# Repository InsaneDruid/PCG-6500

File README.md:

# PCG 6500 - a HAL clone
The PCG 6500 is a 100% compatible clone of the programmable character set generator and sound device for the CBM PET series computers.
It implements all the features, including the ability to reprogram 64 of the PET characters into custom graphics, as well as support for amplified CB2 sound output.

[Schematic](https://github.com/InsaneDruid/PCG-6500/blob/main/6500_board/pcg6500.pdf "Schematic")  

[Bill of Materials](https://htmlpreview.github.io/?https://github.com/InsaneDruid/PCG-6500/blob/main/6500_board/bom/pcg6500_bom.html "Bill of Materials")

## The 6540 Adapter

For PETs using the MOS 6540 rom set, there is an [adapter board](https://github.com/InsaneDruid/PCG-6500/blob/main/6540_adapter "adapter board") that mounts in place of CN1 and allows easy connection to the 6540 charrom using two DIP 28pin to ribbon adapters.

## The SwitchMod
Originally, there was no way to simply disable the HAL PCG 6500 once installed. Katunori Takesita discovered a simple modification that an owner had applied to his board, which consisted of disconnecting an input of a nand-gate from address 9 of the CharROM bus (by cutting a trace) and grounding it instead, effectively disabling the RAM and re-enabling the CharROM permanently. This mod is also implemented in this replica and jumper JP1 is provided for this purpose.

### Enabling the card permanently
Bridge JP1 to permanently enable the card like it was originally.

### The SwitchMod board
A small [SwitchMod board](https://github.com/InsaneDruid/PCG-6500/blob/main/6500_switchMod "SwitchMod board") has been designed providing the ability to switch between the address9 signal and GND for the input of IC8D using an 74LS00, avoiding the need to route the fast address signal over a mechanical switch. This board also has the ability to connect a 3-pin common cathode dual LED (or one or two standard LEDs) to indicate the state of the board. Connect the pins E,A,+,- on the SwitchMod to the corresponding pins on the 6500 board.

## The case
A [3d printable case](https://www.printables.com/model/819722-hal-pcg-6500-case "https://www.printables.com/model/819722-hal-pcg-6500-case") is available at my printables profile.

## Programming the PCG 6500 
Each programmable character provided by the PCG 6500 is programmed line by line via the PETs 6522 peripheral port A (PA7-0), which is available on the user port. PA0-4 transport the actual data, PA 5-7 address the data and address latches on the PCG 6500
See the [Programming chart](https://github.com/InsaneDruid/PCG-6500/blob/main/6500_programming_chart.pdf "Programming chart") originally taken from the PCG 6500 manual with some fixed typos.

## The Software
Software using the PCG-6500 and further documents are available on their own repository: [PCG-6500 Software](https://github.com/InsaneDruid/PCG-6500-Software "Software and Documents for the PCG-6500 Software")

## The License
This work is licensed under a Creative Commons Attribution-ShareAlike 4.0 International License.  
See https://creativecommons.org/licenses/by-sa/4.0/.

## The Credits
This work would not have been possible without the help from a bunch of amazing people from [VzEkC e. V. forums](https://forum.classic-computing.de/forum/ "forum.classic-computing.de") and around the world. Many thanks go out to:

* *AndyG* - for providing images of a working board.
* *Katunori Takesita* - his blog about repairing an original board had important additional images and informations.

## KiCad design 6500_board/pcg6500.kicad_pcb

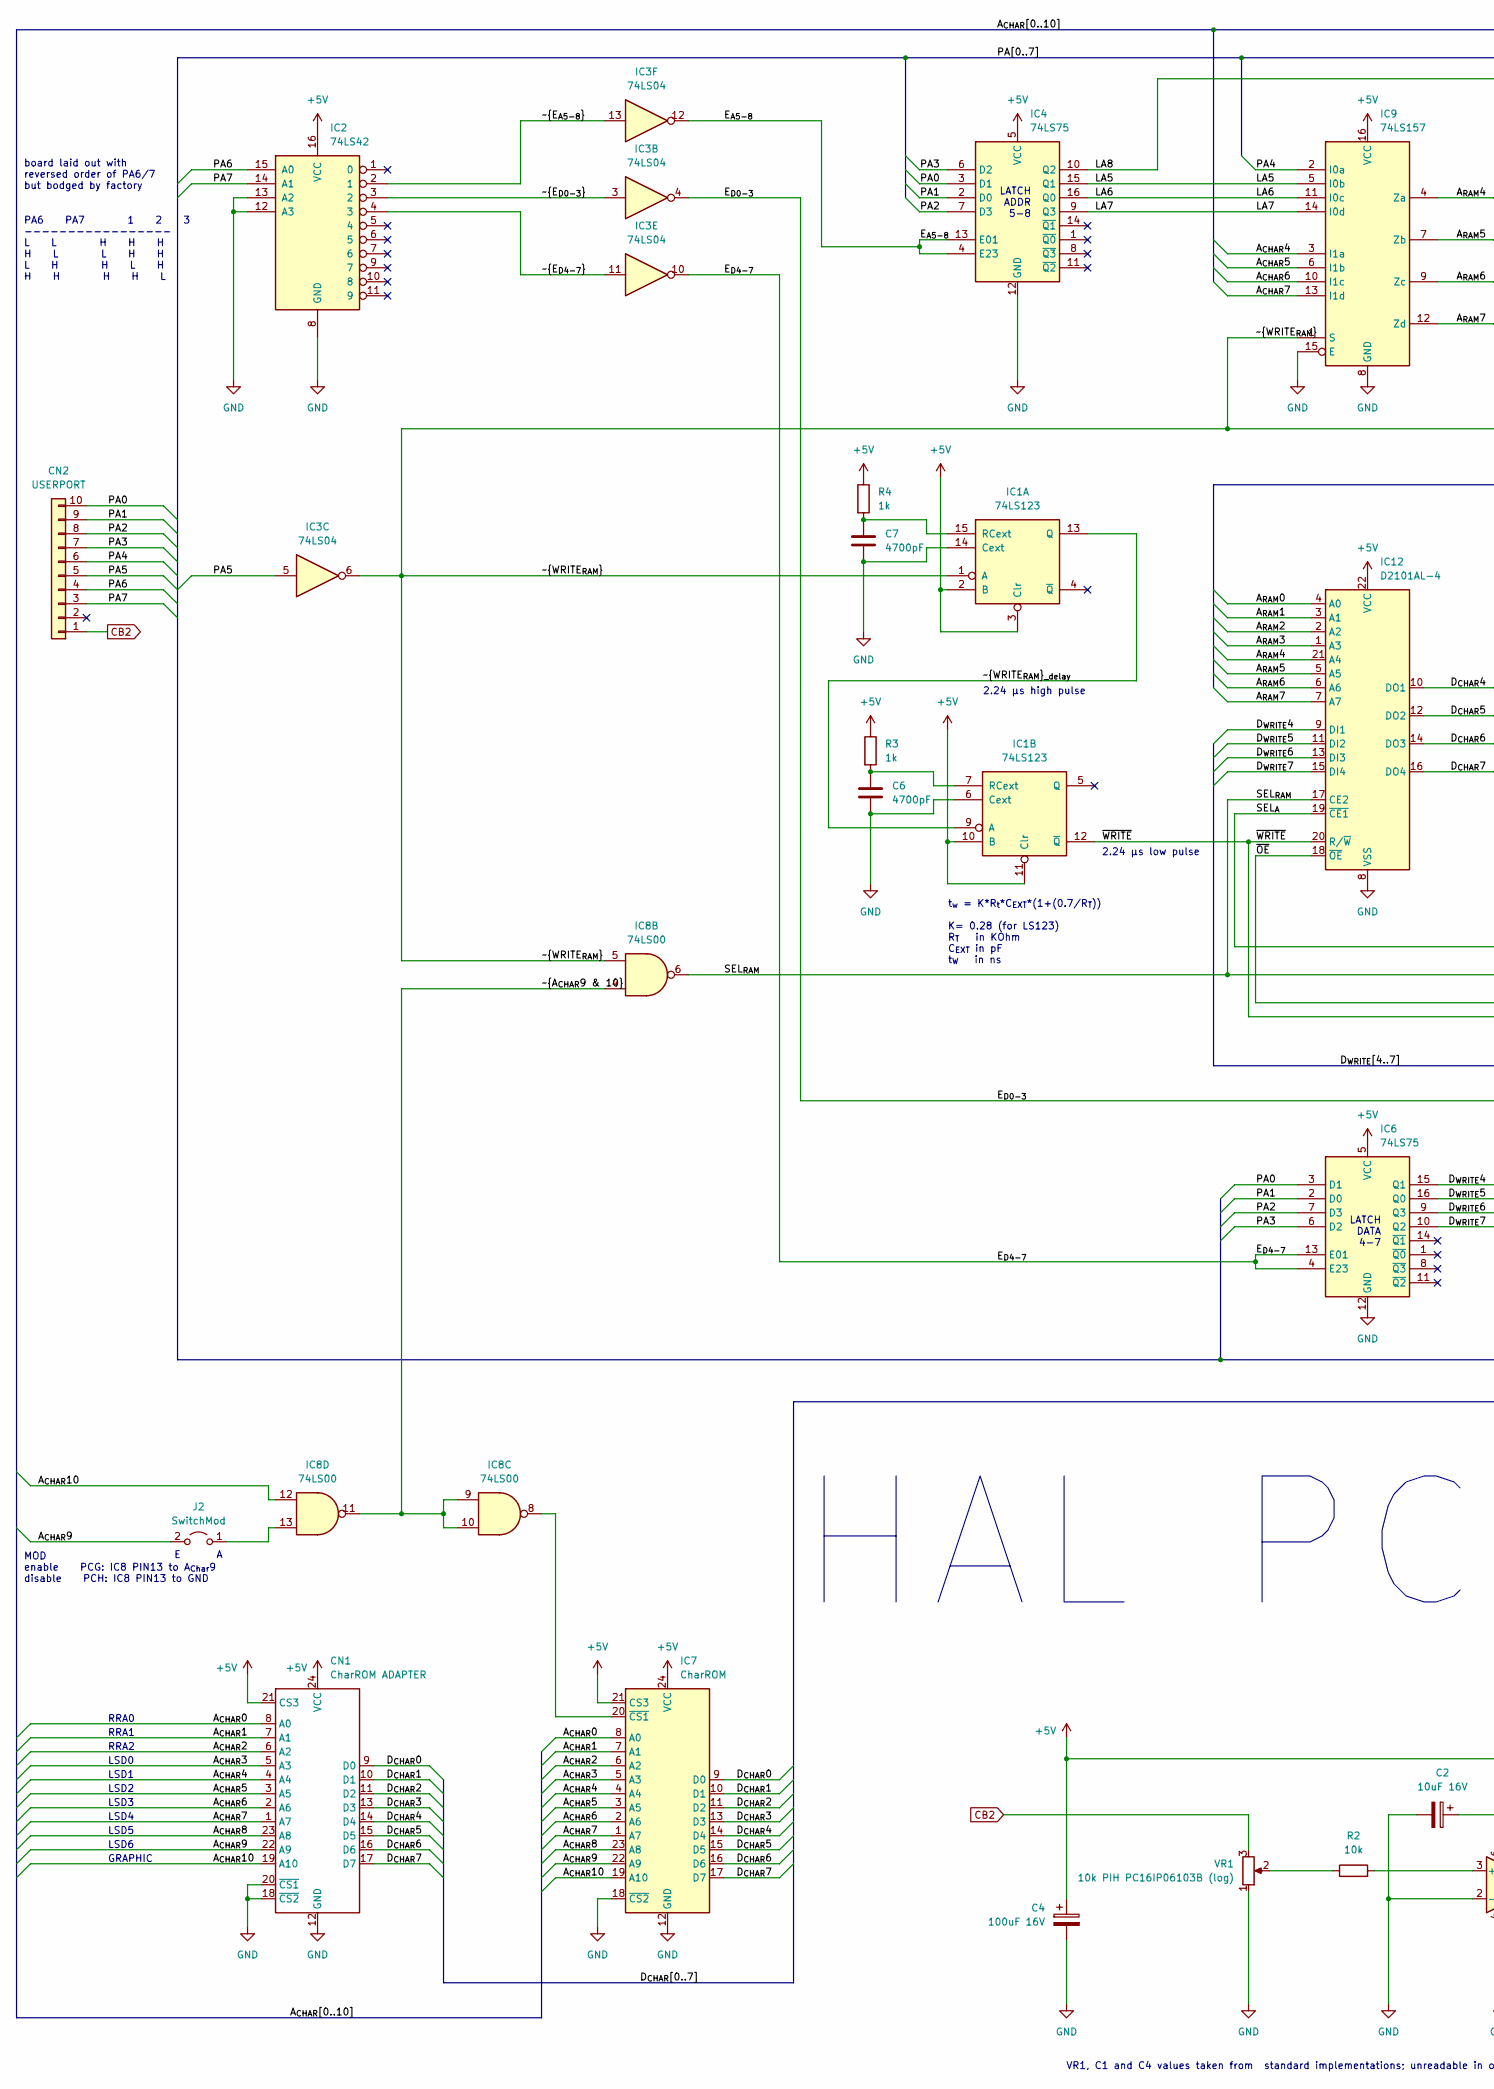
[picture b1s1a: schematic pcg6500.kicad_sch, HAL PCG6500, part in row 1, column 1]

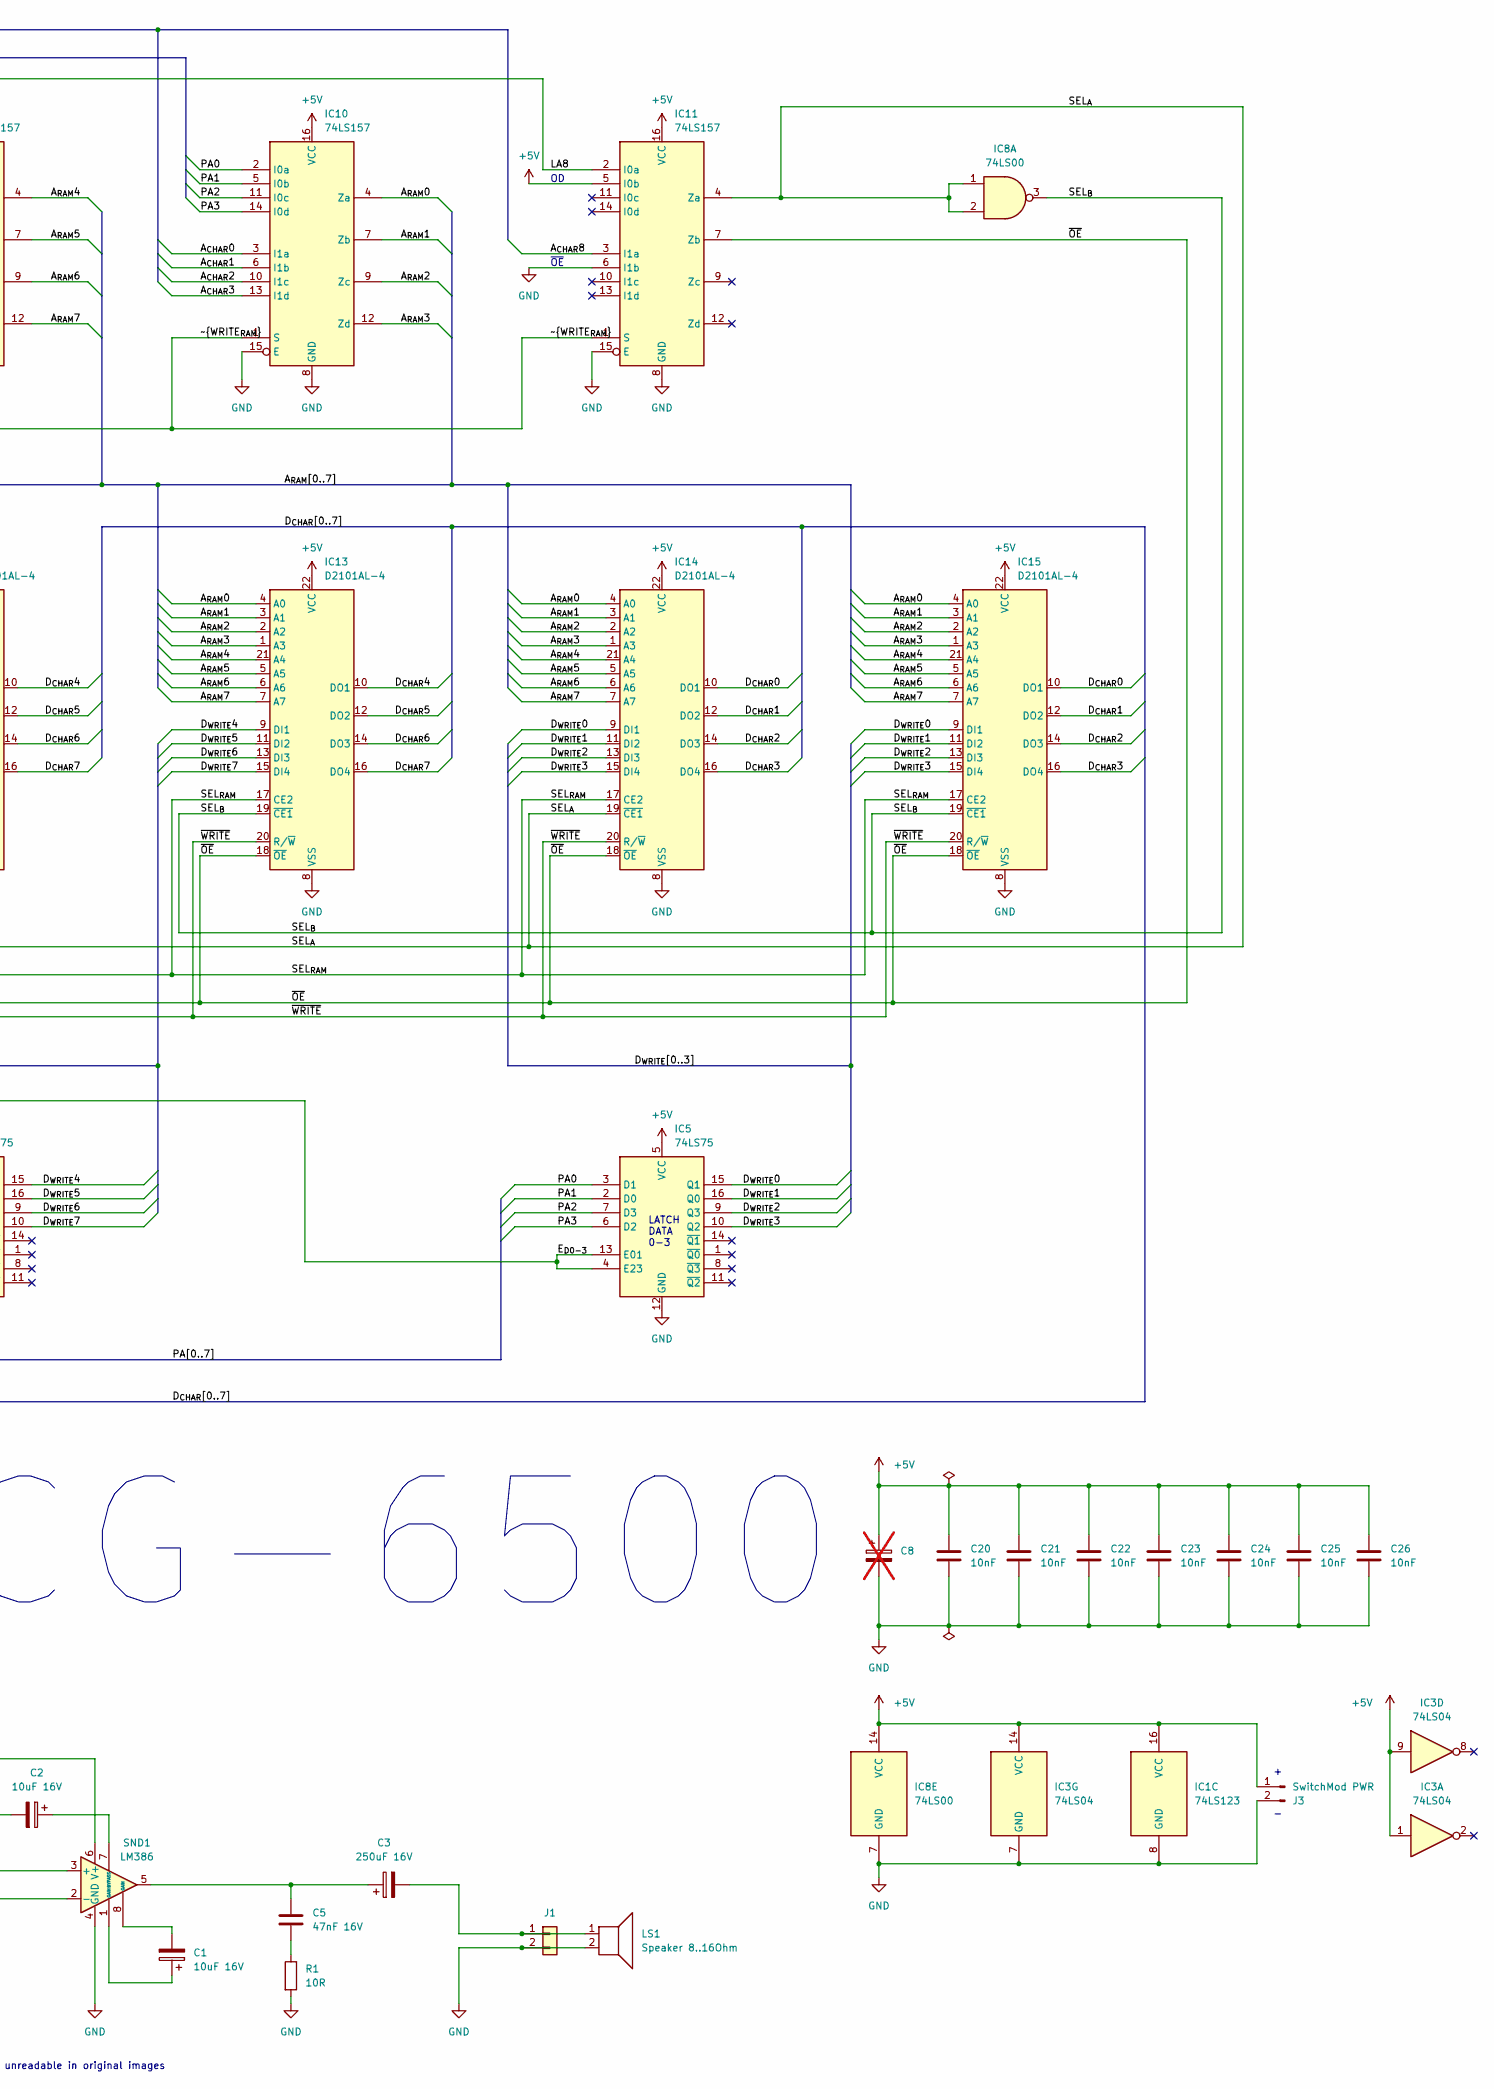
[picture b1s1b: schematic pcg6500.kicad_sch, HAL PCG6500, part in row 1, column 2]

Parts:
C1, C2: 10uF 16V; CP_Radial_D6.3mm_P2.50mm
C3: 250uF 16V; CP_Radial_D10.0mm_P5.00mm
C4: 100uF 16V; CP_Radial_D8.0mm_P5.00mm
C5: 47nF 16V; C_Disc_D4.3mm_W1.9mm_P7.62mm
C6, C7: 4700pF; C_Disc_D4.3mm_W1.9mm_P5.08mm
C8: C_Polarized; CP_Radial_D8.0mm_P5.00mm; not fitted
C20, C21, C22, C23, C24, C25, C26: 10nF; C_Disc_D4.3mm_W1.9mm_P5.08mm_dualpad
CN1: CharROM ADAPTER; DIP-24_W15.24mm_Wire_Adapter
CN2: USERPORT; PinHeader_1x10_P2.54mm_Vertical
IC1: 74LS123; DIP-16_W7.62mm
IC2: 74LS42; DIP-16_W7.62mm
IC3: 74LS04; DIP-14_W7.62mm
IC4, IC5, IC6: 74LS75; DIP-16_W7.62mm
IC7: CharROM; DIP-24_W15.24mm_Socket
IC8: 74LS00; DIP-14_W7.62mm
IC9, IC10, IC11: 74LS157; DIP-16_W7.62mm
IC12, IC13, IC14, IC15: D2101AL-4; DIP-22_W10.16mm
J1: Speaker 8..16Ohm; SolderWire-1sqmm_1x02_P7.8mm_D1.4mm_OD3.9mm
J2: SwitchMod; PinHeader_1x02_P2.54mm_Horizontal
J3: SwitchMod PWR; PinHeader_1x02_P2.54mm_Horizontal
LS1: Speaker 8..16Ohm
R1: 10R; R_Axial_DIN0207_L6.3mm_D2.5mm_P9.2075mm_Horizontal
R2: 10k; R_Axial_DIN0309_L9.0mm_D3.2mm_P12.70mm_Horizontal
R3, R4: 1k; R_Axial_DIN0207_L6.3mm_D2.5mm_P9.2075mm_Horizontal
SND1: LM386; DIP-8_W7.62mm
VR1: 10k PIH PC16IP06103B (log); Potentiometer_Piher_PC-16_Dual_Horizontal

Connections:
+5V: C4.1, C8.1, C20.1, C21.1, C22.1, C23.1, C24.1, C25.2, C26.2, CN1.21 (CS3), CN1.24 (VCC), IC1.2 (B), IC1.3 (Clr), IC1.10 (B), IC1.11 (Clr), IC1.16 (VCC), IC2.16 (VCC), IC3.1, IC3.9, IC3.14 (VCC), IC4.5 (VCC), IC5.5 (VCC), IC6.5 (VCC), IC7.21 (CS3), IC7.24 (VCC), IC8.14 (VCC), IC9.16 (VCC), IC10.16 (VCC), IC11.5 (I0b), IC11.16 (VCC), IC12.22 (VCC), IC13.22 (VCC), IC14.22 (VCC), IC15.22 (VCC), J3.1, R3.1, R4.1, SND1.6 (V+)
/A_{CHAR}0: CN1.8 (A0), IC7.8 (A0), IC10.3 (I1a)
/A_{CHAR}1: CN1.7 (A1), IC7.7 (A1), IC10.6 (I1b)
/A_{CHAR}2: CN1.6 (A2), IC7.6 (A2), IC10.10 (I1c)
/A_{CHAR}3: CN1.5 (A3), IC7.5 (A3), IC10.13 (I1d)
/A_{CHAR}4: CN1.4 (A4), IC7.4 (A4), IC9.3 (I1a)
/A_{CHAR}5: CN1.3 (A5), IC7.3 (A5), IC9.6 (I1b)
/A_{CHAR}6: CN1.2 (A6), IC7.2 (A6), IC9.10 (I1c)
/A_{CHAR}7: CN1.1 (A7), IC7.1 (A7), IC9.13 (I1d)
/A_{CHAR}8: CN1.23 (A8), IC7.23 (A8), IC11.3 (I1a)
/A_{CHAR}9: CN1.22 (A9), IC7.22 (A9), J2.2 (B)
/A_{CHAR}10: CN1.19 (A10), IC7.19 (A10), IC8.12
/A_{RAM}0: IC10.4 (Za), IC12.4 (A0), IC13.4 (A0), IC14.4 (A0), IC15.4 (A0)
/A_{RAM}1: IC10.7 (Zb), IC12.3 (A1), IC13.3 (A1), IC14.3 (A1), IC15.3 (A1)
/A_{RAM}2: IC10.9 (Zc), IC12.2 (A2), IC13.2 (A2), IC14.2 (A2), IC15.2 (A2)
/A_{RAM}3: IC10.12 (Zd), IC12.1 (A3), IC13.1 (A3), IC14.1 (A3), IC15.1 (A3)
/A_{RAM}4: IC9.4 (Za), IC12.21 (A4), IC13.21 (A4), IC14.21 (A4), IC15.21 (A4)
/A_{RAM}5: IC9.7 (Zb), IC12.5 (A5), IC13.5 (A5), IC14.5 (A5), IC15.5 (A5)
/A_{RAM}6: IC9.9 (Zc), IC12.6 (A6), IC13.6 (A6), IC14.6 (A6), IC15.6 (A6)
/A_{RAM}7: IC9.12 (Zd), IC12.7 (A7), IC13.7 (A7), IC14.7 (A7), IC15.7 (A7)
/D_{CHAR}0: CN1.9 (D0), IC7.9 (D0), IC14.10 (DO1), IC15.10 (DO1)
/D_{CHAR}1: CN1.10 (D1), IC7.10 (D1), IC14.12 (DO2), IC15.12 (DO2)
/D_{CHAR}2: CN1.11 (D2), IC7.11 (D2), IC14.14 (DO3), IC15.14 (DO3)
/D_{CHAR}3: CN1.13 (D3), IC7.13 (D3), IC14.16 (DO4), IC15.16 (DO4)
/D_{CHAR}4: CN1.14 (D4), IC7.14 (D4), IC12.10 (DO1), IC13.10 (DO1)
/D_{CHAR}5: CN1.15 (D5), IC7.15 (D5), IC12.12 (DO2), IC13.12 (DO2)
/D_{CHAR}6: CN1.16 (D6), IC7.16 (D6), IC12.14 (DO3), IC13.14 (DO3)
/D_{CHAR}7: CN1.17 (D7), IC7.17 (D7), IC12.16 (DO4), IC13.16 (DO4)
/D_{WRITE}0: IC5.15 (Q1), IC14.9 (DI1), IC15.9 (DI1)
/D_{WRITE}1: IC5.16 (Q0), IC14.11 (DI2), IC15.11 (DI2)
/D_{WRITE}2: IC5.9 (Q3), IC14.13 (DI3), IC15.13 (DI3)
/D_{WRITE}3: IC5.10 (Q2), IC14.15 (DI4), IC15.15 (DI4)
/D_{WRITE}4: IC6.15 (Q1), IC12.9 (DI1), IC13.9 (DI1)
/D_{WRITE}5: IC6.16 (Q0), IC12.11 (DI2), IC13.11 (DI2)
/D_{WRITE}6: IC6.9 (Q3), IC12.13 (DI3), IC13.13 (DI3)
/D_{WRITE}7: IC6.10 (Q2), IC12.15 (DI4), IC13.15 (DI4)
/E_{A5-8}: IC3.12, IC4.4 (E23), IC4.13 (E01)
/E_{D0-3}: IC3.4, IC5.4 (E23), IC5.13 (E01)
/E_{D4-7}: IC3.10, IC6.4 (E23), IC6.13 (E01)
/LA5: IC4.15 (Q1), IC9.5 (I0b)
/LA6: IC4.16 (Q0), IC9.11 (I0c)
/LA7: IC4.9 (Q3), IC9.14 (I0d)
/LA8: IC4.10 (Q2), IC11.2 (I0a)
/PA0: CN2.10, IC4.3 (D1), IC5.3 (D1), IC6.3 (D1), IC10.2 (I0a)
/PA1: CN2.9, IC4.2 (D0), IC5.2 (D0), IC6.2 (D0), IC10.5 (I0b)
/PA2: CN2.8, IC4.7 (D3), IC5.7 (D3), IC6.7 (D3), IC10.11 (I0c)
/PA3: CN2.7, IC4.6 (D2), IC5.6 (D2), IC6.6 (D2), IC10.14 (I0d)
/PA4: CN2.6, IC9.2 (I0a)
/PA5: CN2.5, IC3.5
/PA6: CN2.4, IC2.15 (A0)
/PA7: CN2.3, IC2.14 (A1)
/SEL_{A}: IC8.1, IC8.2, IC11.4 (Za), IC12.19 (~CE1), IC14.19 (~CE1)
/SEL_{B}: IC8.3, IC13.19 (~CE1), IC15.19 (~CE1)
/SEL_{RAM}: IC8.6, IC12.17 (CE2), IC13.17 (CE2), IC14.17 (CE2), IC15.17 (CE2)
/~A_{CHAR9 & 10}: IC8.4, IC8.9, IC8.10, IC8.11
/~E_{A5-8}: IC2.2 (1), IC3.13
/~E_{D0-3}: IC2.3 (2), IC3.3
/~E_{D4-7}: IC2.4 (3), IC3.11
/~OE: IC11.7 (Zb), IC12.18 (~OE), IC13.18 (~OE), IC14.18 (~OE), IC15.18 (~OE)
/~WRITE_{RAM}: IC1.1 (A), IC3.6, IC8.5, IC9.1 (S), IC10.1 (S), IC11.1 (S)
/~WRITE_{RAM}_{_delay}: IC1.9 (A), IC1.13 (Q)
/~WRITE: IC1.12 (~Q), IC12.20 (R/~W), IC13.20 (R/~W), IC14.20 (R/~W), IC15.20 (R/~W)
CB2: CN2.1, VR1.3
GND: C2.2, C4.2, C6.2, C7.2, C8.2, C20.2, C21.2, C22.2, C23.2, C24.2, C25.1, C26.1, CN1.12 (GND), CN1.18 (~CS2), CN1.20 (~CS1), IC1.6 (Cext), IC1.8 (GND), IC1.14 (Cext), IC2.8 (GND), IC2.12 (A3), IC2.13 (A2), IC3.7 (GND), IC4.12 (GND), IC5.12 (GND), IC6.12 (GND), IC7.12 (GND), IC7.18 (~CS2), IC8.7 (GND), IC9.8 (GND), IC9.15 (E), IC10.8 (GND), IC10.15 (E), IC11.6 (I1b), IC11.8 (GND), IC11.15 (E), IC12.8 (VSS), IC13.8 (VSS), IC14.8 (VSS), IC15.8 (VSS), J1.2, J1.12, J1.18, J1.20, J3.2, LS1.2, R1.2, SND1.2 (-), SND1.4 (GND), VR1.1
unnamed: C1.1, SND1.1 (GAIN)
unnamed: C1.2, SND1.8 (GAIN)
unnamed: C3.1, C5.1, SND1.5
unnamed: C5.2, R1.1
unnamed: C7.1, IC1.15 (RCext), R4.2
unnamed: C6.1, IC1.7 (RCext), R3.2
unnamed: IC7.20 (~CS1), IC8.8
unnamed: C3.2, J1.1, LS1.1
unnamed: IC8.13, J2.1 (A)
unnamed: R2.1, VR1.2
unnamed: R2.2, SND1.3 (+)
unnamed: C2.1, SND1.7 (BYPASS)

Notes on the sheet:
LATCH DATA 4-7
board laid out with reversed order of PA6/7 but bodged by factory
LATCH DATA 0-3
LSD2
LATCH ADDR 5-8
2.24 µs low pulse
t_{w} = K*R_{t}*C_{EXT}*(1+(0.7/R_{T})) K= 0.28 (for LS123) R_{T} in KOhm C_{EXT} in pF t_{W} in ns
RRA2
RRA1
GRAPHIC
LSD1
RRA0
LSD0
2.24 µs high pulse
HAL PCG-6500
LSD6
LSD3
LSD5
~{OE}
MOD enable PCG: IC8 PIN13 to A_{Char}9 disable PCH: IC8 PIN13 to GND
LSD4
VR1, C1 and C4 values taken from standard implementations; unreadable in original images
PA6 PA7 1 2 3 ----------------- L L H H H H L L H H L H H L H H H H H L

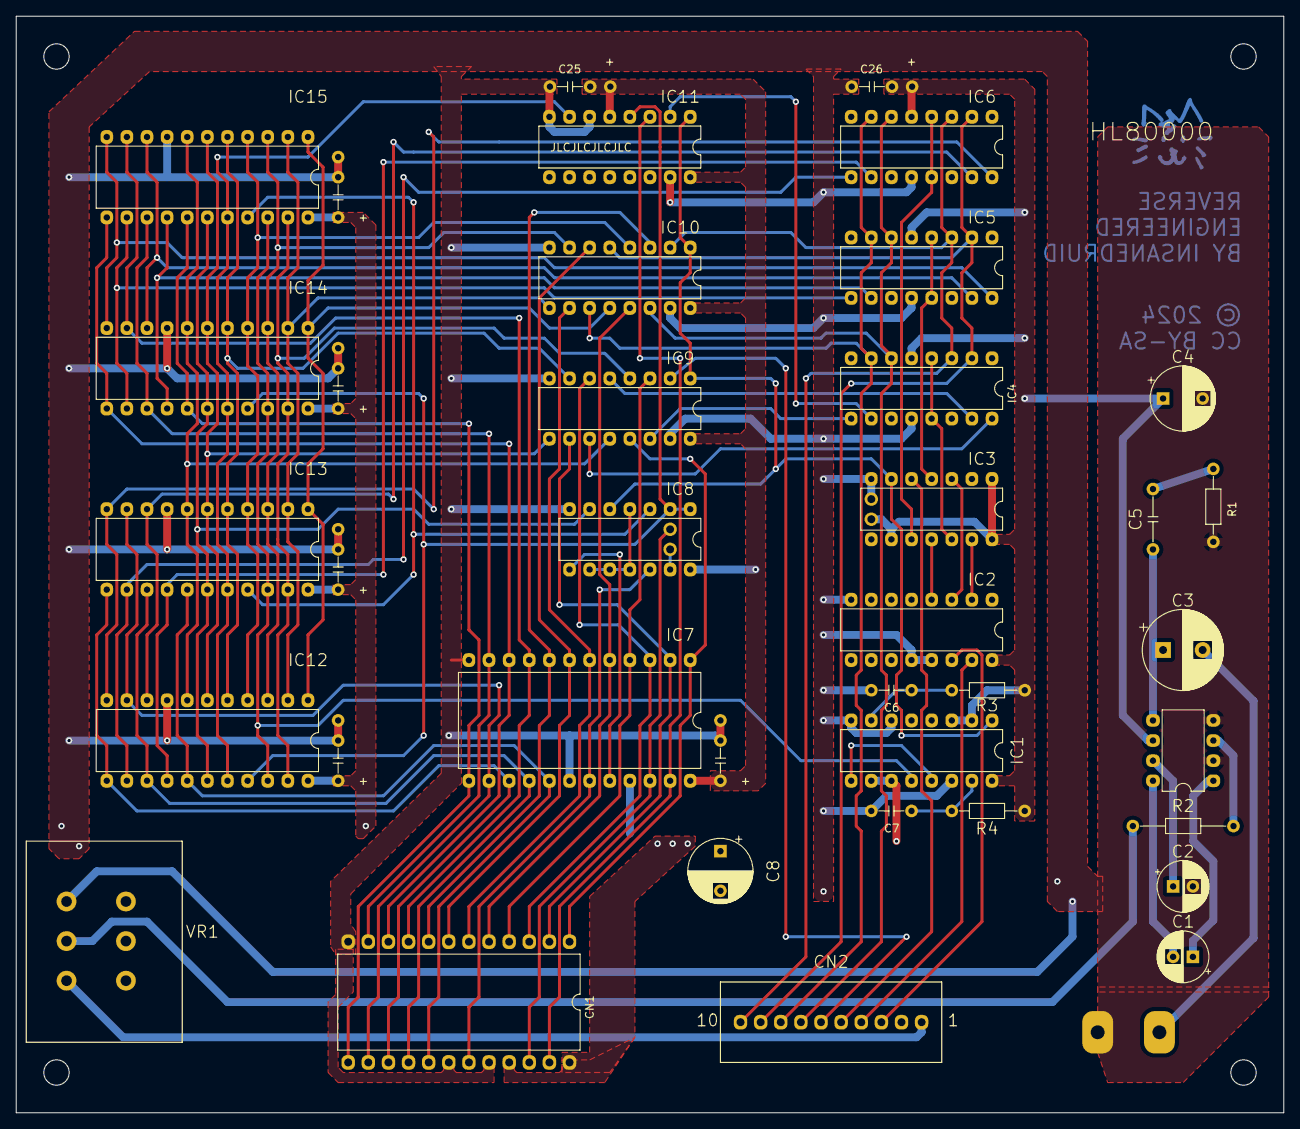
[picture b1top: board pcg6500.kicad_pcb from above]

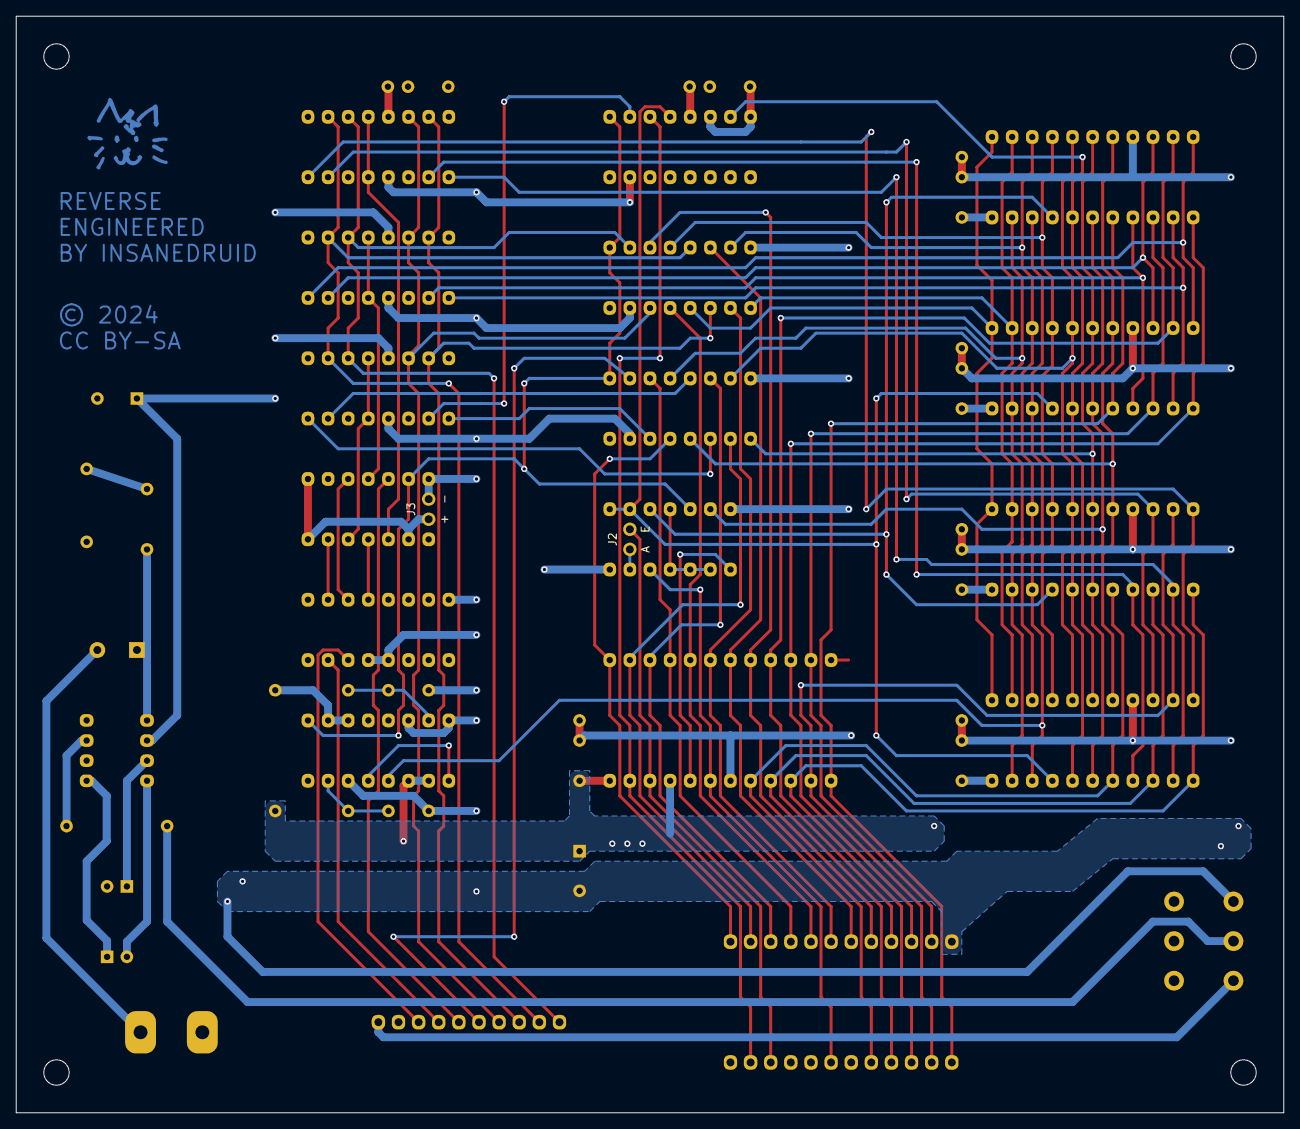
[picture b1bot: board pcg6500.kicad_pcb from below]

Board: 2 copper layers, 160.0 x 138.4 mm, 45 parts (2 on the bottom side), 76 nets.

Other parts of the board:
Mountinghole_BL: MountingHole_3.2mm_M3_DIN965
Mountinghole_BR: MountingHole_3.2mm_M3_DIN965
Mountinghole_TL: MountingHole_3.2mm_M3_DIN965
Mountinghole_TR: MountingHole_3.2mm_M3_DIN965

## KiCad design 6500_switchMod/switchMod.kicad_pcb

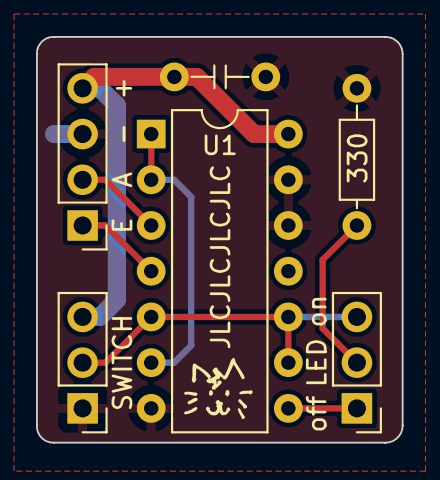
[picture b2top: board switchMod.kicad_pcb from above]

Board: 2 copper layers, 20.3 x 22.5 mm, 6 parts (0 on the bottom side), 8 nets.

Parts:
C1: 100nF; C_Disc_D4.3mm_W1.9mm_P5.08mm
J1: 6500 Connector; PinHeader_1x04_P2.54mm_Vertical
J2: Switch Connector; PinHeader_1x03_P2.54mm_Vertical
J3: LED Connector; PinHeader_1x03_P2.54mm_Vertical
R1: 330R; R_Axial_DIN0207_L6.3mm_D2.5mm_P7.62mm_Horizontal
U1: 74LS00; DIP-14_W7.62mm

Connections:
/A9: J1.1, U1.4
/A9_{switched}: J1.2, U1.3
/ENABLE: J2.2, J3.3, U1.5, U1.9, U1.10
/LED_{COMMON}: J3.2, R1.2
/LED_{OFF}: J3.1, U1.8
GND: C1.2, J1.3, J2.1, R1.1, U1.7 (GND), U1.12, U1.13
unnamed: U1.1, U1.2, U1.6
VCC: C1.1, J1.4, J2.3, U1.14 (VCC)

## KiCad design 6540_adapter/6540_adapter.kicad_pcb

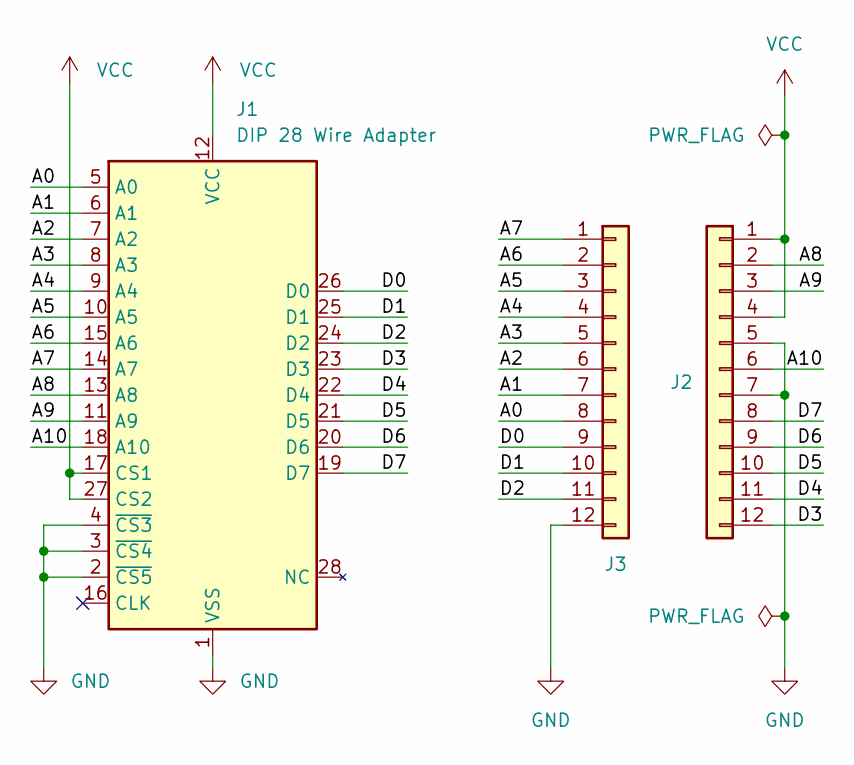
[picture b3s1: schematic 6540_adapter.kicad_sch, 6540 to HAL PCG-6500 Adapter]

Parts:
J1: DIP 28 Wire Adapter; DIP-28_W15.24mm_Wire_Adapter
J2, J3: Conn_01x12; PinHeader_1x12_P2.54mm_Vertical

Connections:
/A0: J1.5 (A0), J3.8
/A1: J1.6 (A1), J3.7
/A2: J1.7 (A2), J3.6
/A3: J1.8 (A3), J3.5
/A4: J1.9 (A4), J3.4
/A5: J1.10 (A5), J3.3
/A6: J1.15 (A6), J3.2
/A7: J1.14 (A7), J3.1
/A8: J1.13 (A8), J2.2
/A9: J1.11 (A9), J2.3
/A10: J1.18 (A10), J2.6
/D0: J1.26 (D0), J3.9
/D1: J1.25 (D1), J3.10
/D2: J1.24 (D2), J3.11
/D3: J1.23 (D3), J2.12
/D4: J1.22 (D4), J2.11
/D5: J1.21 (D5), J2.10
/D6: J1.20 (D6), J2.9
/D7: J1.19 (D7), J2.8
GND: J1.1 (VSS), J1.2 (~CS5), J1.3 (~CS4), J1.4 (~CS3), J2.5, J2.7, J3.12
VCC: J1.12 (VCC), J1.17 (CS1), J1.27 (CS2), J2.1, J2.4

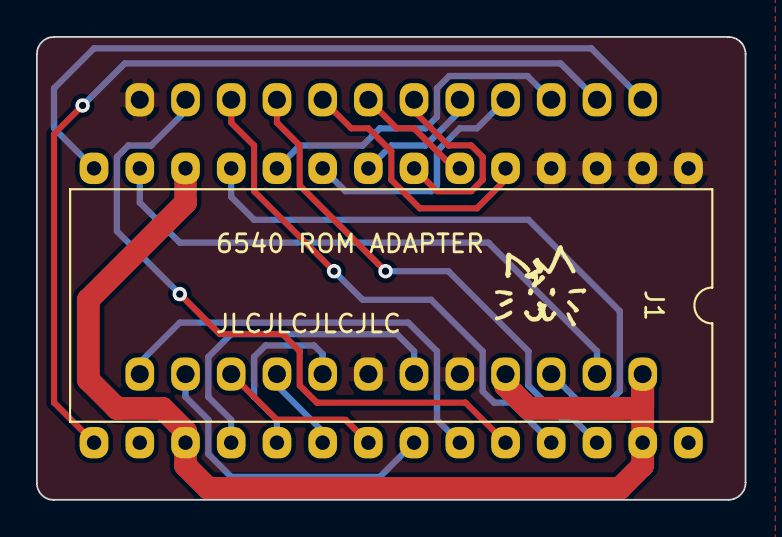
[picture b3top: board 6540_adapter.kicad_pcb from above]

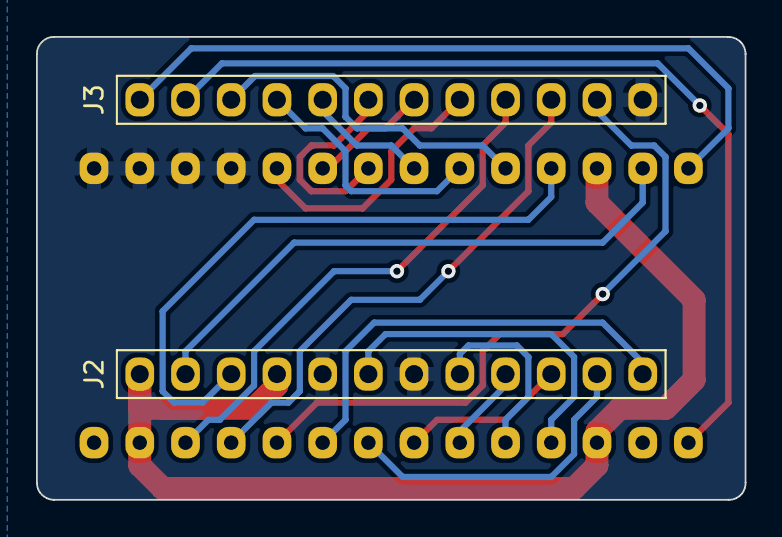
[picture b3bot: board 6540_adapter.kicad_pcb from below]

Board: 2 copper layers, 39.4 x 25.7 mm, 3 parts (2 on the bottom side), 21 nets.

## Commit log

2024-10-08 Update 6500_programming_chart.pdf
    address bit 4 was missing
2024-10-08 housekeeping
    added missing Cap values
    improvements in signal naming and schematic layout
    no functional changes
2024-11-02 BOM adjustment
    - changed excessive voltage rating of audio related capacitors to more realistic values
    - added cn2 connector to bom

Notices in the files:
6500_board/pcg6500.kicad_pcb:
License: CC BY-SA 4.0
© 2024
CC BY-SA
